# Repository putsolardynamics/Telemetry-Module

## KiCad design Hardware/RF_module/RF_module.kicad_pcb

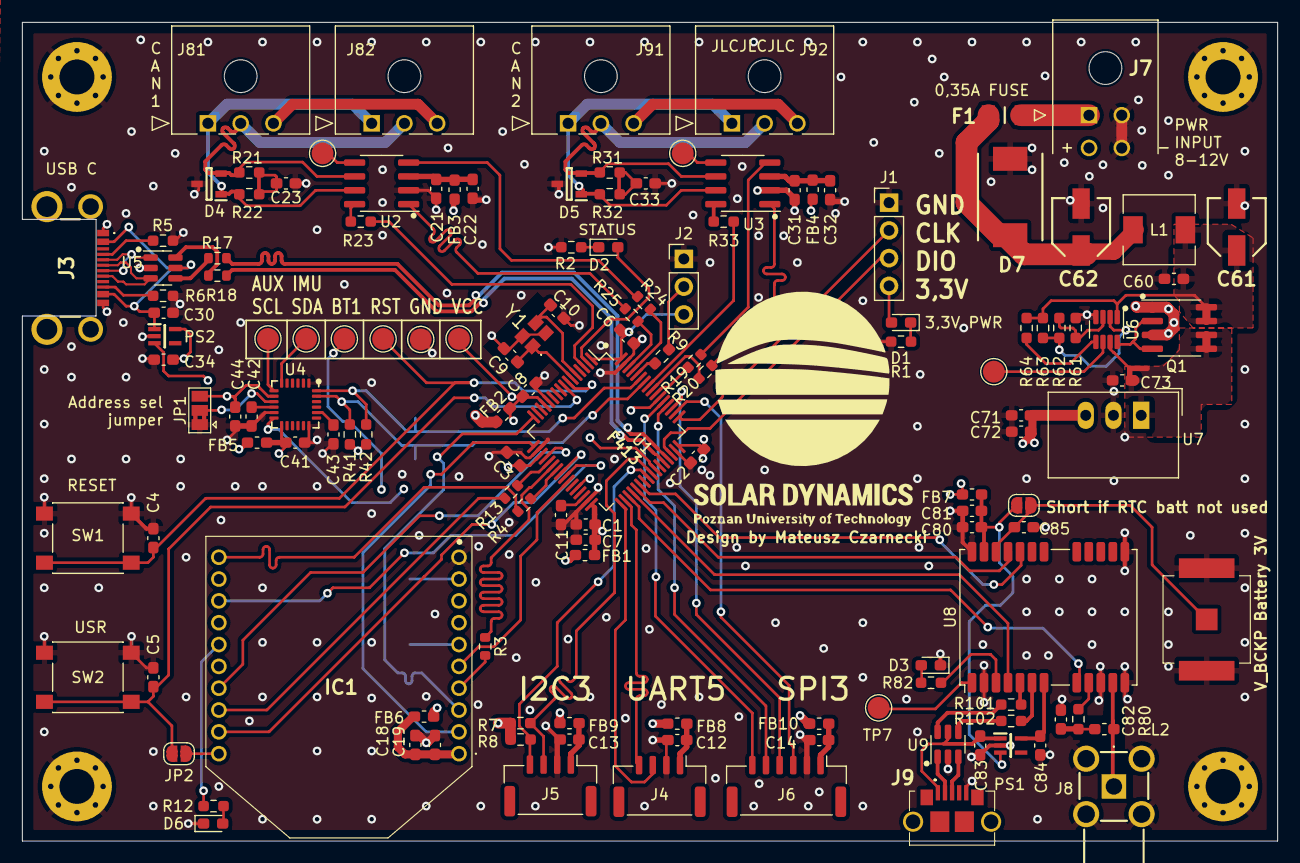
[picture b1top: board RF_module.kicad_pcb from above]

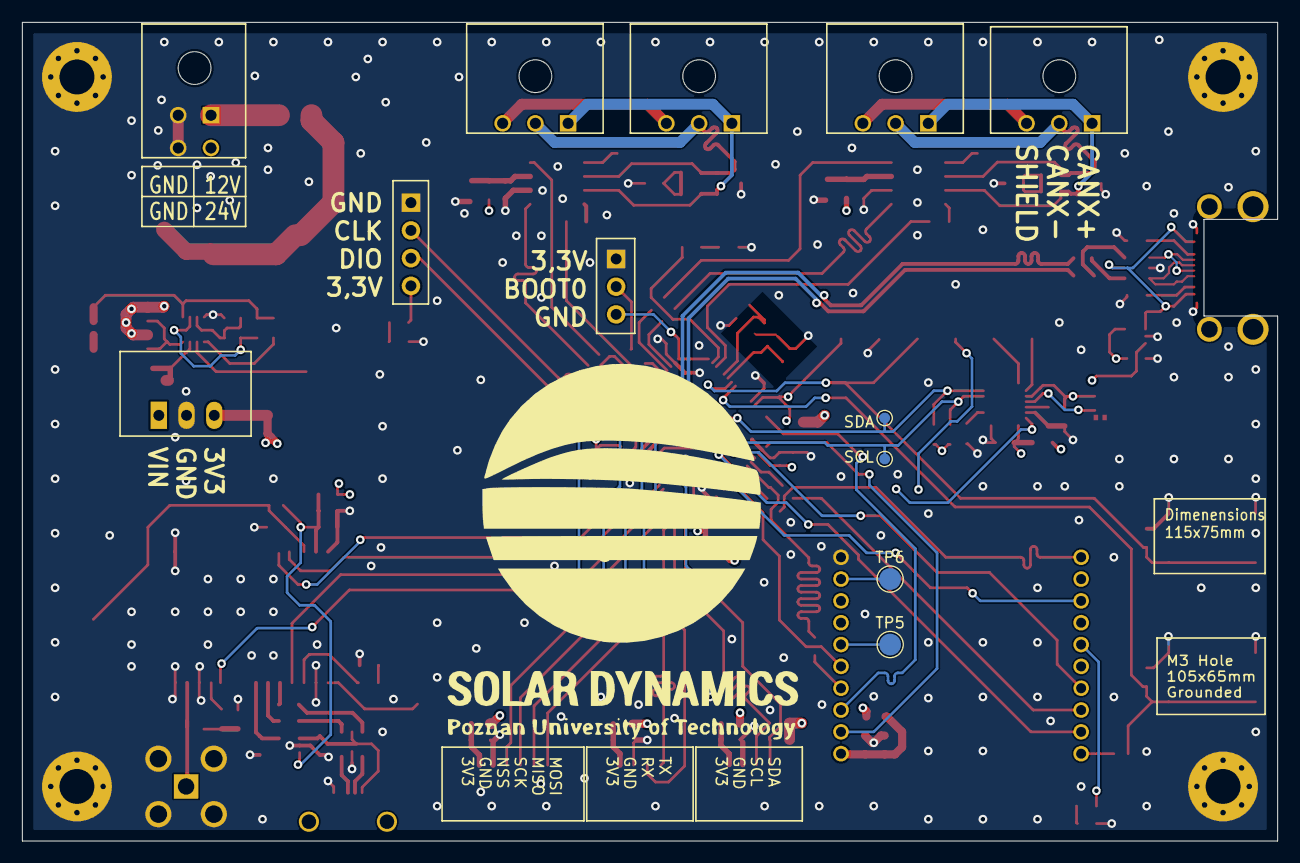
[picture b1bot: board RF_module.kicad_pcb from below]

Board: 4 copper layers, 115.0 x 75.0 mm, 144 parts (4 on the bottom side), 118 nets.

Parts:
C1, C11, C19, C22, C32, C44, C71, C73, C81: 4.7u; C_0603_1608Metric_Pad1.08x0.95mm_HandSolder
C2, C3, C4, C5, C6, C7, C8, C18, C21, C31, C41, C42, C72: 100n; C_0603_1608Metric_Pad1.08x0.95mm_HandSolder
C9, C10: 10p; C_0603_1608Metric_Pad1.08x0.95mm_HandSolder
C12, C13, C14, C30, C34, C60, C80, C83, C84, C85: 1u; C_0603_1608Metric_Pad1.08x0.95mm_HandSolder
C23, C33, C82: 4.7n; C_0603_1608Metric_Pad1.08x0.95mm_HandSolder
C43: 2.2n; C_0603_1608Metric_Pad1.08x0.95mm_HandSolder
C61, C62: 10u; EEE0GA101SR
D1: LED RED; LED_0603_1608Metric_Pad1.05x0.95mm_HandSolder
D2, D3, D6: LED BLUE; LED_0603_1608Metric_Pad1.05x0.95mm_HandSolder
D4, D5: PESD1CAN,215; SOT95P230X110-3N
D7: ESD TWS; DIONM7959X262N
F1: 0ZCJ0035AF2E; FUSC3216X130N
FB1, FB2, FB3, FB4, FB5, FB6, FB7, FB8, FB9, FB10: FerriteBead_Small; L_0603_1608Metric_Pad1.05x0.95mm_HandSolder
H1, H2, H3, H4: M3; MountingHole_3.2mm_M3_Pad_Via
IC1: XB3-24Z8UT-J; XB324Z8UTJ
J1: SWD; PinHeader_1x04_P2.54mm_Vertical
J2: BOOT_SEL; PinHeader_1x03_P2.54mm_Vertical
J3: USB_C_Receptacle_USB2.0; USB4500030A
J4: UART4; JST_GH_BM04B-GHS-TBT_1x04-1MP_P1.25mm_Vertical
J5: I2C3; JST_GH_BM04B-GHS-TBT_1x04-1MP_P1.25mm_Vertical
J6: SPI3; JST_GH_BM06B-GHS-TBT_1x06-1MP_P1.25mm_Vertical
J7: Molex Power; 43045-04_00,01,02,10_
J8: SMA; 518144002
J9: USB3075-30-A; USB307530A
J10: 2998TR
J81, J82, J91, J92: 436500300
JP1: SolderJumper_3_Open; SolderJumper-3_P1.3mm_Bridged2Bar12_Pad1.0x1.5mm
JP2, JP80: SolderJumper_2_Open; SolderJumper-2_P1.3mm_Open_RoundedPad1.0x1.5mm
L1: L; L_6.3x6.3_H3
L2: 27n; L_0603_1608Metric_Pad1.05x0.95mm_HandSolder
PS1, PS2: MIC5365-3.3YC5-TR; SOT65P210X110-5N
Q1: FDS6898A; SOIC-8_3.9x4.9mm_P1.27mm
R1, R2, R9, R12, R82: 330; R_0603_1608Metric_Pad0.98x0.95mm_HandSolder
R3, R4, R13, R17, R18, R19, R20, R24, R25: 0; R_0603_1608Metric
R5, R6: 5.1K; R_0603_1608Metric_Pad0.98x0.95mm_HandSolder
R7, R8, R41, R42: 4.7K; R_0603_1608Metric_Pad0.98x0.95mm_HandSolder
R21, R22, R31, R32: 62; R_0603_1608Metric_Pad0.98x0.95mm_HandSolder
R23, R33: 510; R_0603_1608Metric_Pad0.98x0.95mm_HandSolder
R61, R64: 133K; R_0603_1608Metric_Pad0.98x0.95mm_HandSolder
R62: 167K; R_0603_1608Metric_Pad0.98x0.95mm_HandSolder
R63: 4.5M; R_0603_1608Metric_Pad0.98x0.95mm_HandSolder
R80, R101, R102: 10; R_0603_1608Metric_Pad0.98x0.95mm_HandSolder
SW1: SW_RST; SW_Push_1P1T_NO_6x6mm_H9.5mm
SW2: SW_USR; SW_Push_1P1T_NO_6x6mm_H9.5mm
TP1: FAULT; TestPoint_Pad_D2.0mm
TP2: NRST; TestPoint_Pad_D2.0mm
TP3: BOOT1; TestPoint_Pad_D2.0mm
TP4: VCC; TestPoint_Pad_D2.0mm
TP5: RSSI_PWM; TestPoint_Pad_D2.0mm
TP6: SLEEP_RQ; TestPoint_Pad_D2.0mm
TP7: SAFEBOOT; TestPoint_Pad_D2.0mm
TP21: Vref2; TestPoint_Pad_D2.0mm
TP31: Vref3; TestPoint_Pad_D2.0mm
TP41: IMU_AUX_SDA; TestPoint_Pad_D2.0mm
TP42: IMU_AUX_SCL; TestPoint_Pad_D2.0mm
TP234: GND; TestPoint_Pad_D2.0mm
TP_SDA: TestPoint_Pad_D1.0mm
TP_SDA#2: TestPoint_Pad_D1.0mm
U1: STM32F413RHT6; LQFP-64_10x10mm_P0.5mm
U2, U3: SN65HVD231; SOIC-8_3.9x4.9mm_P1.27mm
U4: MPU-6050; InvenSense_QFN-24_4x4mm_P0.5mm
U5, U9: USBLC6-2SC6; SOT-23-6
U6: LTC4365xTS8; TSOT-23-8
U7: TSR_1-2433; Converter_DCDC_TRACO_TSR-1_THT
U8: NEO-M9N; ublox_NEO
Y1: ECS-160-10-36 16MHz; ECS1601036CKMTR3

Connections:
+3.3V: C71.1, C72.1, D1.2 (A), FB1.1, FB2.1, FB3.1, FB4.1, FB5.2, FB6.1, FB7.1, FB8.1, FB9.1, FB10.1, J1.4, PS2.3 (EN), R7.1, R8.1, U7.3 (Vout)
+12V: C73.1, Q1.5 (D2), Q1.6 (D2), U6.7 (VOUT), U7.1 (Vin)
/CAN BUS/3.3V_CAN1: C21.1, C22.1, FB3.2, U2.3 (VCC)
/CAN BUS/3.3V_CAN2: C31.1, C32.1, FB4.2, U3.3 (VCC)
/CAN BUS/CAN1+: D4.1 (CATHODE_1), J81.1, J82.1, R22.1, U2.7 (CANH)
/CAN BUS/CAN1-: D4.2 (CATHODE_2), J81.2, J82.2, R21.1, U2.6 (CANL)
/CAN BUS/CAN1_RS: R23.2, U1.3 (PC14)
/CAN BUS/CAN1_RX: R24.2, U2.4 (R)
/CAN BUS/CAN1_TX: R25.2, U2.1 (D)
/CAN BUS/CAN3+: D5.1 (CATHODE_1), J91.1, J92.1, R32.1, U3.7 (CANH)
/CAN BUS/CAN3-: D5.2 (CATHODE_2), J91.2, J92.2, R31.1, U3.6 (CANL)
/CAN BUS/CAN3_RS: R33.2, U1.57 (PB5)
/CAN BUS/CAN3_RX: R19.2, U3.4 (R)
/CAN BUS/CAN3_TX: R20.2, U3.1 (D)
/CAN BUS/SHIELD1: J81.3, J82.3
/CAN BUS/SHIELD2: J91.3, J92.3
/CONNECTORS/CC1: J3.A5 (CC1), R5.1
/CONNECTORS/CC2: J3.B5 (CC2), R6.1
/CONNECTORS/D+: J3.A6 (D+), J3.B6 (D+), U5.3 (I/O2)
/CONNECTORS/D-: J3.A7 (D-), J3.B7 (D-), U5.1 (I/O1)
/CONNECTORS/I2C3_SCL: J5.3, R7.2, U1.41 (PA8)
/CONNECTORS/I2C3_SDA: J5.4, R8.2, U1.40 (PC9)
/CONNECTORS/SPI3_MISO: J6.5, U1.52 (PC11)
/CONNECTORS/SPI3_MOSI: J6.6, U1.53 (PC12)
/CONNECTORS/SPI3_NSS: J6.3, U1.50 (PA15)
/CONNECTORS/SPI3_SCK: J6.4, U1.51 (PC10)
/CONNECTORS/UART5_RX: J4.3, U1.33 (PB12)
/CONNECTORS/UART5_TX: J4.4, U1.34 (PB13)
/CONNECTORS/USB_D+: R17.1, U5.4 (I/O2)
/CONNECTORS/USB_D-: R18.1, U5.6 (I/O1)
/CONNECTORS/USB_VBUS_DET: C34.1, PS2.5 (VOUT), U1.42 (PA9)
/CONNECTORS/VBUS: C30.1, J3.A4 (VBUS), J3.A9 (VBUS), PS2.1 (VIN), U5.5 (VBUS)
/GNSS/3.3V_GPS: C80.1, C81.1, FB7.2, JP80.2 (B), PS1.3 (EN), U8.23 (VCC)
/GNSS/GPS_EXTINT: U1.36 (PB15), U8.4 (EXTINT)
/GNSS/GPS_PULSE: R82.1, U8.3 (TIMEPULSE)
/GNSS/GPS_RST: U1.35 (PB14), U8.8 (~RESET)
/GNSS/GPS_RX: U1.37 (PC6), U8.21 (RXD/SPI_MOSI)
/GNSS/GPS_TX: U1.38 (PC7), U8.20 (TXD/SPI_MISO)
/GNSS/USB_DM: R101.1, U9.6 (I/O1)
/GNSS/USB_DP: R102.1, U9.4 (I/O2)
/GNSS/VDD_USB: C84.1, PS1.5 (VOUT), U8.7 (VDD_USB)
/GNSS/V_BCKP: C85.1, J10.3, JP80.1 (A), U8.22 (V_BCKP)
/IMU/3.3V_IMU: C41.1, C44.1, FB5.1, JP1.3 (B), R41.1, R42.1, U4.8 (VDDIO), U4.13 (VDD)
/IMU/IMU_INT: U1.54 (PD2), U4.12 (INT)
/IMU/IMU_SCL: R41.2, TP_SDA.1, U1.58 (PB6), U4.23 (SCL)
/IMU/IMU_SDA: R42.2, TP_SDA#2.1, U1.59 (PB7), U4.24 (SDA)
/MCU/BOOT0: R9.2, U1.60 (BOOT0)
/MCU/BOOT1: TP3.1, U1.28 (PB2)
/MCU/CAN1_RX: R24.1, U1.61 (PB8)
/MCU/CAN1_TX: R25.1, U1.62 (PB9)
/MCU/CAN3_RX: R19.1, U1.55 (PB3)
/MCU/CAN3_TX: R20.1, U1.56 (PB4)
/MCU/NRST: C4.1, SW1.2, TP2.1, U1.7 (NRST)
/MCU/SPI1_ATT: IC1.19 (AD1/DIO1/SPI_~ATTN), U1.24 (PC4)
/MCU/SPI1_MISO: R3.1, U1.22 (PA6)
/MCU/SPI1_MOSI: R4.1, U1.23 (PA7)
/MCU/SPI1_NSS: IC1.17 (AD3/DIO3/SPI_~SSEL), U1.20 (PA4)
/MCU/SPI1_SCK: R13.1, U1.21 (PA5)
/MCU/SWCLK: J1.2, U1.49 (PA14)
/MCU/SWDIO: J1.3, U1.46 (PA13)
/MCU/SYS_LED: D2.2 (A), U1.2 (PC13)
/MCU/USART2_RX: IC1.2 (DOUT/DIO13), U1.17 (PA3)
/MCU/USART2_TX: IC1.3 (DIN/~CONFIG/DIO14), U1.16 (PA2)
/MCU/USB_D+: R17.2, U1.45 (PA12)
/MCU/USB_D-: R18.2, U1.44 (PA11)
/MCU/XBEE_RST: IC1.5 (~RESET), U1.26 (PB0)
/MCU/XBEE_SLEEP: IC1.13 (ON/~SLEEP/DIO9), U1.25 (PC5)
/POWER SUPPLY/+BATT_F: C60.1, C61.1, L1.2, Q1.7 (D1), Q1.8 (D1), R63.1, R64.1, U6.1 (VIN)
/POWER SUPPLY/GATE: Q1.2 (G1), Q1.4 (G2), U6.8 (GATE)
/XBEE/3.3V_XBEE: C18.1, C19.1, FB6.2, IC1.1 (VCC)
/XBEE/XBEE_LED: IC1.15 (ASSOCIATE/DIO5), R12.1
/XBEE/XBEE_MISO: IC1.4 (DIO12/SPI_MISO), R3.2
/XBEE/XBEE_MOSI: IC1.11 (DIO4/SPI_MOSI), R4.2
/XBEE/XBEE_SCK: IC1.18 (AD2/DIO2/SPI_CLK), R13.2
GND: C1.2, C2.2, C3.2, C4.2, C5.2, C6.2, C7.2, C8.2, C9.2, C10.2, C11.2, C12.1, C13.1, C14.1, C18.2, C19.2, C21.2, C22.2, C23.2, C30.2, C31.2, C32.2, C33.2, C34.2, C41.2, C42.2, C43.2, C44.2, C60.2, C61.2, C62.2, C71.2, C72.2, C73.2, C80.2, C81.2, C82.2, C83.2, C84.2, C85.2, D3.1 (K), D4.3 (COMMON_CATHODE), D5.3 (COMMON_CATHODE), D6.1 (K), D7.2, H1.1, H2.1, H3.1, H4.1, IC1.10 (GND), J1.1, J2.1, J3.A1 (GND), J3.A12 (GND), J4.2, J5.2, J6.2, J7.2, J7.4, J8.2 (Ext), J9.5, J10.1, J10.2, JP1.1 (A), PS1.2 (GND), PS2.2 (GND), R1.2, R2.2, R5.2, R6.2, R61.2, SW1.1, SW2.1, TP234.1, U1.12 (VSSA), U1.18 (VSS), U1.31 (VSS), U1.47 (VSS), U1.63 (VSS), U2.2 (GND), U3.2 (GND), U4.1 (CLKIN), U4.11 (FSYNC), U4.18 (GND), U5.2 (GND), U6.4 (GND), U7.2 (GND), U8.2 (D_SEL), U8.10 (GND), U8.12 (GND), U8.13 (GND), U8.24 (GND), U9.2 (GND), Y1.2 (GND_1), Y1.4 (GND_2)
unnamed: C23.1, R21.2, R22.2
unnamed: C33.1, R31.2, R32.2
unnamed: C62.1, D7.1, F1.2, L1.1
unnamed: C82.1, L2.1, R80.2
unnamed: D1.1 (K), R1.1
unnamed: D2.1 (K), R2.1
unnamed: D3.2 (A), R82.2
unnamed: D6.2 (A), R12.2
unnamed: F1.1, J7.1
unnamed: IC1.20 (AD0_/DIO0), JP2.1 (A)
unnamed: IC1.6 (RSSI_PWM/DIO10), TP5.1
unnamed: IC1.9 (~DTR/SLEEP_RQ/DIO8), TP6.1
unnamed: J2.2, R9.1
unnamed: C12.2, FB8.2, J4.1
unnamed: C13.2, FB9.2, J5.1
unnamed: C14.2, FB10.2, J6.1
unnamed: J8.1 (In), L2.2, U8.11 (RF_IN)
unnamed: J9.2, U9.1 (I/O1)
unnamed: J9.3, U9.3 (I/O2)
unnamed: JP1.2 (C), U4.9 (AD0)
unnamed: C83.1, J9.1, PS1.1 (VIN), U9.5 (VBUS)
unnamed: Q1.1 (S1), Q1.3 (S2)
unnamed: C10.1, U1.5 (PH0), Y1.3 (OUT/IN)
unnamed: C9.1, U1.6 (PH1), Y1.1 (IN/OUT)
unnamed: C11.1, U1.30 (VCAP_1)
unnamed: R23.1, U2.8 (Rs)
unnamed: TP21.1, U2.5 (Vref)
unnamed: R33.1, U3.8 (Rs)
unnamed: TP31.1, U3.5 (Vref)
unnamed: TP42.1, U4.7 (AUX_SCL)
unnamed: TP41.1, U4.6 (AUX_SDA)
unnamed: C43.1, U4.20 (CPOUT)
unnamed: C42.1, U4.10 (REGOUT)
unnamed: R61.1, R62.1, U6.3 (OV)
unnamed: R62.2, R63.2, U6.2 (UV)
unnamed: TP1.1, U6.6 (~FAULT)
unnamed: R64.2, U6.5 (~SHDN)
unnamed: R101.2, U8.5 (USB_DM)
unnamed: R102.2, U8.6 (USB_DP)
unnamed: R80.1, U8.9 (VCC_RF)
unnamed: TP7.1, U8.1 (~SAFEBOOT)
USR_BTN: C5.1, JP2.2 (B), SW2.2, U1.8 (PC0)
VCC: C1.1, C2.1, C3.1, C6.1, C7.1, C8.1, FB1.2, FB2.2, J2.3, TP4.1, U1.1 (VBAT), U1.13 (VDDA), U1.19 (VDD), U1.32 (VDD), U1.48 (VDD), U1.64 (VDD)

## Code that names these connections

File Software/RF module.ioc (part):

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Mcu.Name=STM32F413R(G-H)Tx
Mcu.Package=LQFP64
Mcu.UserName=STM32F413RHTx
PA10.GPIOParameters=GPIO_Label
PA10.GPIO_Label=GPS_SEL
PA10.Signal=GPIO_Output
PA11.Mode=Device_Only
PA11.Signal=USB_OTG_FS_DM
PA12.Mode=Device_Only
PA12.Signal=USB_OTG_FS_DP
PA13.Mode=Serial_Wire
PA13.Signal=SYS_JTMS-SWDIO
PA14.Mode=Serial_Wire
PA14.Signal=SYS_JTCK-SWCLK
PA15.Mode=NSS_Signal_Hard_Output
PA15.Signal=SPI3_NSS
PA2.Mode=Asynchronous
PA2.Signal=USART2_TX
PA3.Mode=Asynchronous
PA3.Signal=USART2_RX
PA4.Mode=NSS_Signal_Hard_Output
PA4.Signal=SPI1_NSS
PA5.Mode=Full_Duplex_Master
PA5.Signal=SPI1_SCK
PA6.Mode=Full_Duplex_Master
PA6.Signal=SPI1_MISO
PA7.Mode=Full_Duplex_Master
PA7.Signal=SPI1_MOSI
PA8.Mode=I2C
PA8.Signal=I2C3_SCL
PA9.Mode=Activate_VBUS
PA9.Signal=USB_OTG_FS_VBUS
PB0.GPIOParameters=GPIO_Label
PB0.GPIO_Label=XBEE_RST
PB0.Signal=GPIO_Output
PB12.Mode=Asynchronous
PB12.Signal=UART5_RX
PB13.Mode=Asynchronous
PB13.Signal=UART5_TX
PB14.GPIOParameters=GPIO_Label
PB14.GPIO_Label=GPS_RST
PB14.Signal=GPIO_Output
PB15.GPIOParameters=GPIO_Label
PB15.GPIO_Label=GPS_EXTINT
PB15.Signal=GPIO_Output
PB3.Mode=CAN_Activate
PB3.Signal=CAN3_RX
PB4.Mode=CAN_Activate
PB4.Signal=CAN3_TX
PB5.GPIOParameters=GPIO_Label
PB5.GPIO_Label=CAN3_RS
PB5.Signal=GPIO_Output
PB6.Mode=I2C
PB6.Signal=I2C1_SCL
PB7.Mode=I2C
PB7.Signal=I2C1_SDA
PB8.Mode=CAN_Activate
PB8.Signal=CAN1_RX
PB9.Mode=CAN_Activate
PB9.Signal=CAN1_TX
PC0.GPIOParameters=GPIO_Label
PC0.GPIO_Label=USR_BTN
PC0.Signal=GPIO_Input
PC10.Mode=Full_Duplex_Master
PC10.Signal=SPI3_SCK
PC11.Mode=Full_Duplex_Master
PC11.Signal=SPI3_MISO
PC12.Mode=Full_Duplex_Master
PC12.Signal=SPI3_MOSI
PC13.GPIOParameters=GPIO_Label
PC13.GPIO_Label=SYS_LED
PC13.Signal=GPIO_Output
PC14-OSC32_IN.GPIOParameters=GPIO_Label
PC14-OSC32_IN.GPIO_Label=CAN1_RS
PC14-OSC32_IN.Signal=GPIO_Output
PC4.GPIOParameters=GPIO_Label
PC4.GPIO_Label=SPI1_ATT
PC4.Signal=GPIO_Input
PC5.GPIOParameters=GPIO_Label
PC5.GPIO_Label=XBEE_SLEEP
PC5.Signal=GPIO_Output
PC6.Mode=Asynchronous
PC6.Signal=USART6_TX
PC7.Mode=Asynchronous
PC7.Signal=USART6_RX
PC8.GPIOParameters=GPIO_Label
PC8.GPIO_Label=GPS_PULSE
PC8.Signal=GPIO_Input
PC9.Mode=I2C
PC9.Signal=I2C3_SDA
PD2.GPIOParameters=GPIO_Label
PD2.GPIO_Label=IMU_INT
PD2.Signal=GPIO_Output
PH0\ -\ OSC_IN.Mode=HSE-External-Oscillator
PH0\ -\ OSC_IN.Signal=RCC_OSC_IN
PH1\ -\ OSC_OUT.Mode=HSE-External-Oscillator
PH1\ -\ OSC_OUT.Signal=RCC_OSC_OUT
board=custom

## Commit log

2023-03-06 Import files
    Initial and probably final revision
2023-05-05 Add files via upload
    added bom from new generator and pick and place
2023-11-04 Debug release build
    First code working on STM using CubeMX project file and VS code
2023-11-06 Change in toolset to PIO with stm32pio
    How I done it is described on slite
2024-04-18 added flake
2024-04-23 added flake for stm32pio
2024-04-24 working flake environment
2024-04-24 added env folders to .gitignore
2024-04-24 nixos project setup
2024-04-24 dma tests
2024-08-14 added ra-07h software
2024-08-14 removed garbage comments
2024-08-14 fixed readme
2024-08-14 logic fixes
2024-08-14 queue refactor
2024-08-14 slow communication working
2024-08-14 everything working
2024-08-14 esp32 reciever
2024-08-14 comms fully working
2024-08-14 got rid of .pio builds

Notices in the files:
parts and their libraries:
Copyright 2021 Accelerated Designs. All rights reserved.
